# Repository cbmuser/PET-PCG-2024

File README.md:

# PET-PCG-2024
In the early 80th HAL Laboratory in Japan created a programmable character set generator and sound device for PET/CBM computers. This used the userport and the charater-socket for connection. So it was very easy to use with the first BASIC 1 machines. 
Mike Naberenzy reversed the logic and reassembled the software. A big thanks for that !  
http://mikenaberezny.com/hardware/pet-cbm/hal-pcg-6500-graphics-board/

It's also possible to rebuild the original hardware: https://github.com/InsaneDruid/PCG-6500 for the early BASIC1-machines. There you'll find also other usefull stuff for your PET.

My version fits into the newer dynamic PET-board (CBM 2001/3001) and uses DMA-access at **$a000** or $9000 for transfering the chars. There is no CB2-sound, I want to combine this in the future with a joystick-adapter at the userport.

You can use a IDT7130 in DIP or PLCC52. **You only need one of them !**  
The actual hardware is not tested in all cases (on/off function). Basically it works and new software is under construction, also some games from the HAL-adapter will be patched to this version. The board-routing was done in development-progress, so it works, but it's not the best it can be.  

**This is open hard- and software. Use it on your own risc. There is no warranty at all !**

The first board for development. The first idea was to use banking for addressing the whole ram and the bigger IDT7132. I've kicked this because no one will ever write software for that.

The char-rom and the connection to the socket fits on the solder-side.

A first character-editor 

It uses $a000 for the DMA. If you want to compile it for $9000 use the ACME Cross-Assembler. https://sourceforge.net/projects/acme-crossass/

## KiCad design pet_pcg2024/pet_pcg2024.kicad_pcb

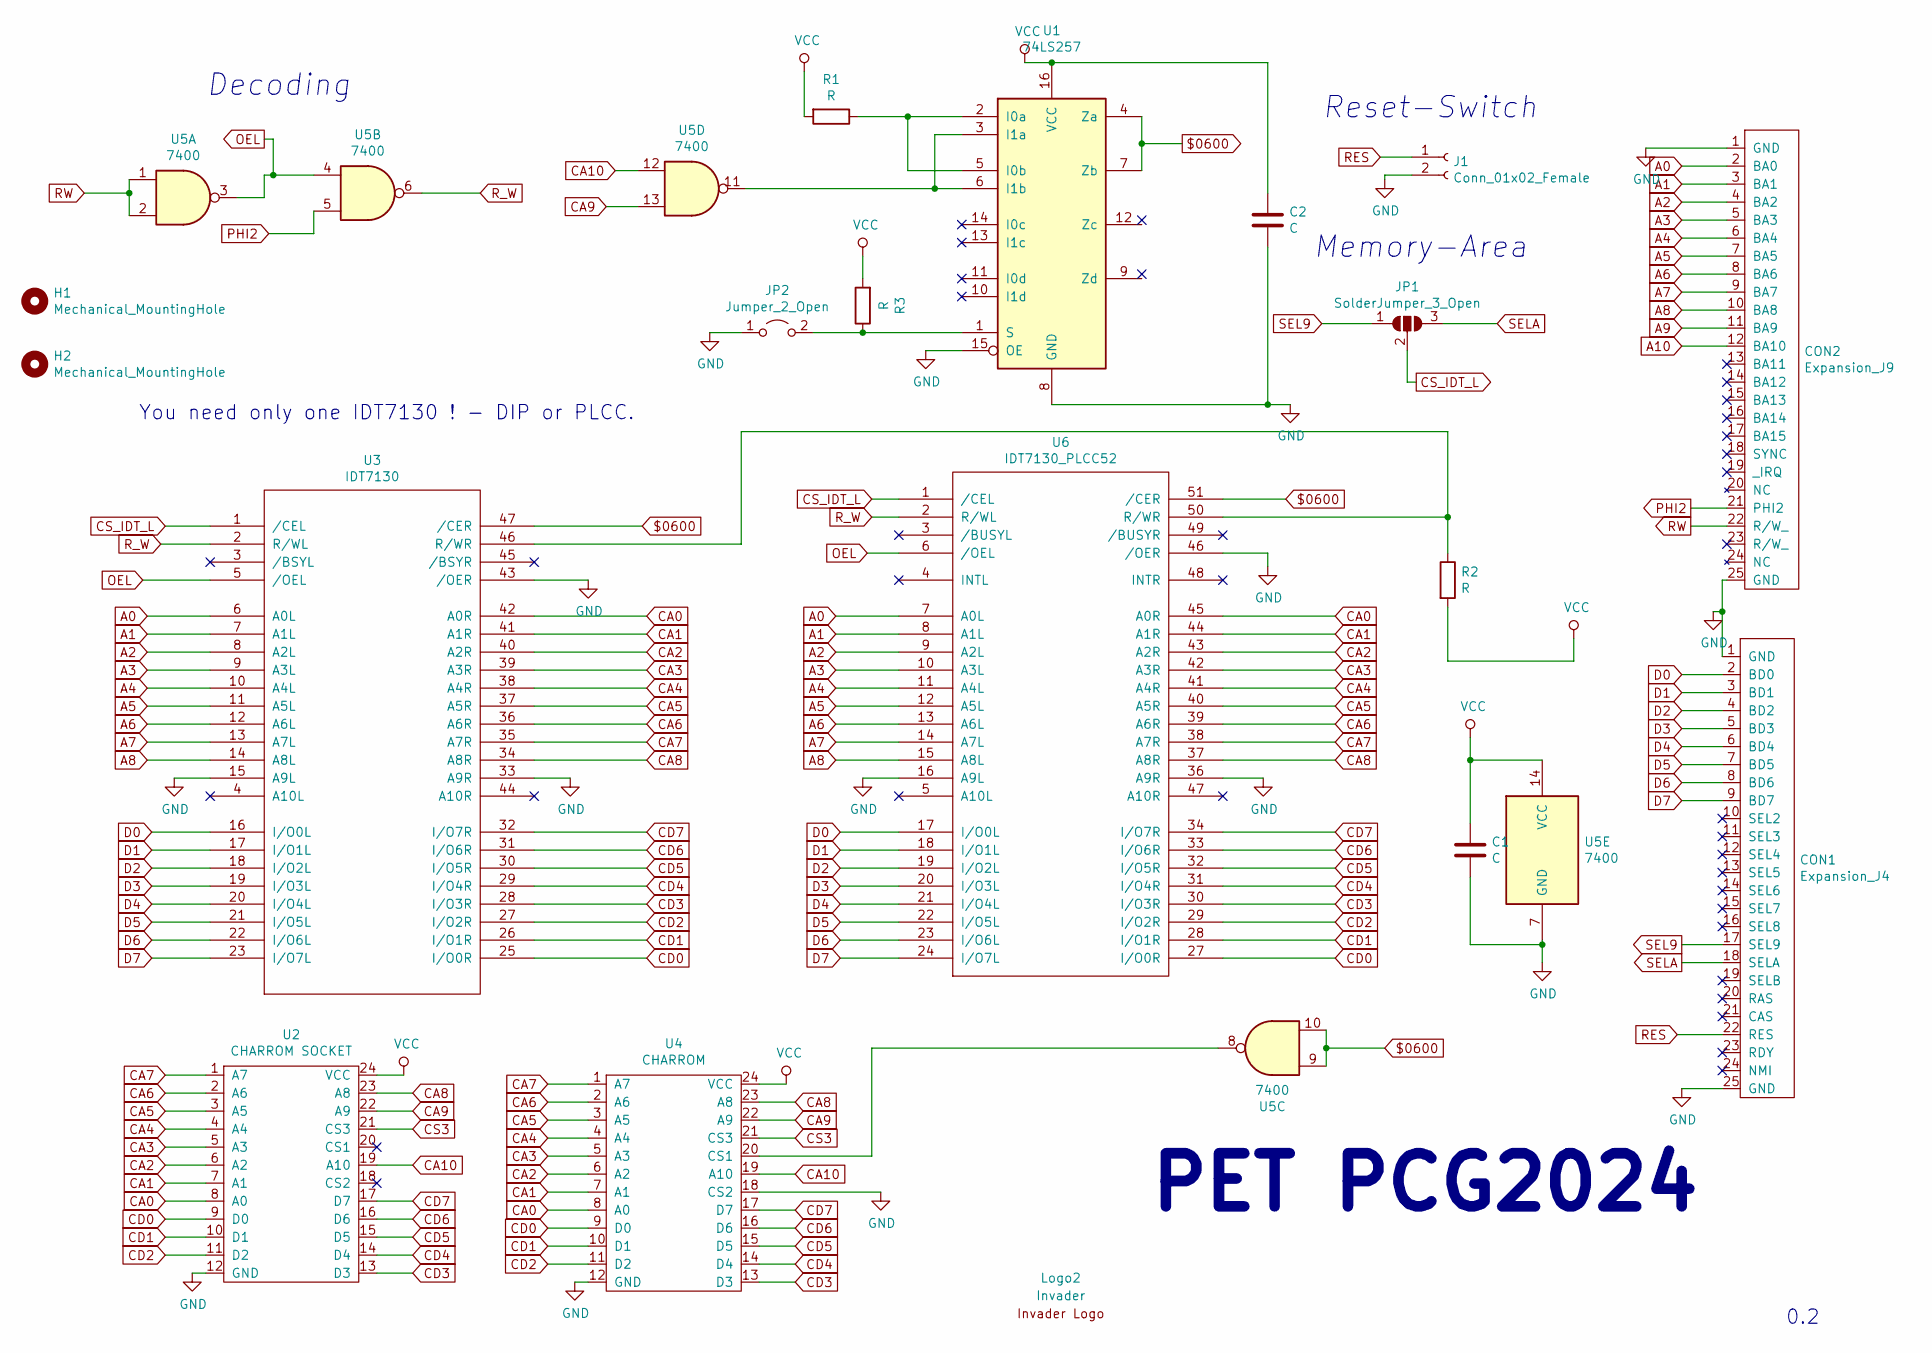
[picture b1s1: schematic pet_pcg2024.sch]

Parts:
C1, C2: C; C_Disc_D3.0mm_W1.6mm_P2.50mm
CON1: Expansion_J4; PET_EXPANSION_J4
CON2: Expansion_J9; PET_EXPANSION_J9
H1, H2: Mechanical_MountingHole; MountingHole_3.2mm_M3
J1: Conn_01x02_Female; PinHeader_1x02_P2.54mm_Vertical
JP1: SolderJumper_3_Open; SolderJumper-3_P1.3mm_Open_Pad1.0x1.5mm
JP2: Jumper_2_Open; PinHeader_1x02_P2.54mm_Vertical
Logo2: Invader; Invader_klein
R1, R3: R; R_Axial_DIN0204_L3.6mm_D1.6mm_P2.54mm_Vertical
R2: R; R_Axial_DIN0204_L3.6mm_D1.6mm_P1.90mm_Vertical
U1: 74LS257; DIP-16_W7.62mm
U2: CHARROM SOCKET; DIP-24_W15.24mm
U3: IDT7130; DIP-48_W15.24mm
U4: CHARROM; DIP-24_W15.24mm_Socket
U5: 7400; DIP-14_W7.62mm
U6: IDT7130_PLCC52; PLCC-52_THT-Socket

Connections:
$0600: U1.4 (Za), U1.7 (Zb), U3.47 (/CER), U5.9, U5.10, U6.51 (/CER)
A0: CON2.2 (BA0), U3.6 (A0L), U6.7 (A0L)
A1: CON2.3 (BA1), U3.7 (A1L), U6.8 (A1L)
A2: CON2.4 (BA2), U3.8 (A2L), U6.9 (A2L)
A3: CON2.5 (BA3), U3.9 (A3L), U6.10 (A3L)
A4: CON2.6 (BA4), U3.10 (A4L), U6.11 (A4L)
A5: CON2.7 (BA5), U3.11 (A5L), U6.12 (A5L)
A6: CON2.8 (BA6), U3.12 (A6L), U6.13 (A6L)
A7: CON2.9 (BA7), U3.13 (A7L), U6.14 (A7L)
A8: CON2.10 (BA8), U3.14 (A8L), U6.15 (A8L)
A9: CON2.11 (BA9)
A10: CON2.12 (BA10)
CA0: U2.8 (A0), U3.42 (A0R), U4.8 (A0), U6.45 (A0R)
CA1: U2.7 (A1), U3.41 (A1R), U4.7 (A1), U6.44 (A1R)
CA2: U2.6 (A2), U3.40 (A2R), U4.6 (A2), U6.43 (A2R)
CA3: U2.5 (A3), U3.39 (A3R), U4.5 (A3), U6.42 (A3R)
CA4: U2.4 (A4), U3.38 (A4R), U4.4 (A4), U6.41 (A4R)
CA5: U2.3 (A5), U3.37 (A5R), U4.3 (A5), U6.40 (A5R)
CA6: U2.2 (A6), U3.36 (A6R), U4.2 (A6), U6.39 (A6R)
CA7: U2.1 (A7), U3.35 (A7R), U4.1 (A7), U6.38 (A7R)
CA8: U2.23 (A8), U3.34 (A8R), U4.23 (A8), U6.37 (A8R)
CA9: U2.22 (A9), U4.22 (A9), U5.13
CA10: U2.19 (A10), U4.19 (A10), U5.12
CD0: U2.9 (D0), U3.25 (I/O0R), U4.9 (D0), U6.27 (I/O0R)
CD1: U2.10 (D1), U3.26 (I/O1R), U4.10 (D1), U6.28 (I/O1R)
CD2: U2.11 (D2), U3.27 (I/O2R), U4.11 (D2), U6.29 (I/O2R)
CD3: U2.13 (D3), U3.28 (I/O3R), U4.13 (D3), U6.30 (I/O3R)
CD4: U2.14 (D4), U3.29 (I/O4R), U4.14 (D4), U6.31 (I/O4R)
CD5: U2.15 (D5), U3.30 (I/O5R), U4.15 (D5), U6.32 (I/O5R)
CD6: U2.16 (D6), U3.31 (I/O6R), U4.16 (D6), U6.33 (I/O6R)
CD7: U2.17 (D7), U3.32 (I/O7R), U4.17 (D7), U6.34 (I/O7R)
CS3: U2.21 (CS3), U4.21 (CS3)
CS_IDT_L: JP1.2 (C), U3.1 (/CEL), U6.1 (/CEL)
D0: CON1.2 (BD0), U3.16 (I/O0L), U6.17 (I/O0L)
D1: CON1.3 (BD1), U3.17 (I/O1L), U6.18 (I/O1L)
D2: CON1.4 (BD2), U3.18 (I/O2L), U6.19 (I/O2L)
D3: CON1.5 (BD3), U3.19 (I/O3L), U6.20 (I/O3L)
D4: CON1.6 (BD4), U3.20 (I/O4L), U6.21 (I/O4L)
D5: CON1.7 (BD5), U3.21 (I/O5L), U6.22 (I/O5L)
D6: CON1.8 (BD6), U3.22 (I/O6L), U6.23 (I/O6L)
D7: CON1.9 (BD7), U3.23 (I/O7L), U6.24 (I/O7L)
GND: C1.2, C2.2, CON1.1 (GND), CON1.25 (GND), CON2.1 (GND), CON2.25 (GND), J1.2, JP2.1 (A), U1.8 (GND), U1.15 (OE), U2.12 (GND), U3.15 (A9L), U3.24 (GND), U3.33 (A9R), U3.43 (/OER), U4.12 (GND), U4.18 (CS2), U5.7 (GND), U6.16 (A9L), U6.26 (GND), U6.36 (A9R), U6.46 (/OER)
unnamed: JP2.2 (B), R3.1, U1.1 (S)
unnamed: R1.1, U1.2 (I0a), U1.5 (I0b)
unnamed: R2.1, U3.46 (R/WR), U6.50 (R/WR)
unnamed: U1.3 (I1a), U1.6 (I1b), U5.11
unnamed: U4.20 (CS1), U5.8
OEL: U3.5 (/OEL), U5.3, U5.4, U6.6 (/OEL)
PHI2: CON2.21 (PHI2), U5.5
RES: CON1.22 (RES), J1.1
RW: CON2.22 (R/W_), U5.1, U5.2
R_W: U3.2 (R/WL), U5.6, U6.2 (R/WL)
SEL9: CON1.17 (SEL9), JP1.1 (A)
SELA: CON1.18 (SELA), JP1.3 (B)
VCC: C1.1, C2.1, R1.2, R2.2, R3.2, U1.16 (VCC), U2.24 (VCC), U3.48 (VCC), U4.24 (VCC), U5.14 (VCC), U6.52 (VCC)

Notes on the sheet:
PET PCG2024
Reset-Switch
Decoding
Memory-Area
You need only one IDT7130 ! - DIP or PLCC.
0.2

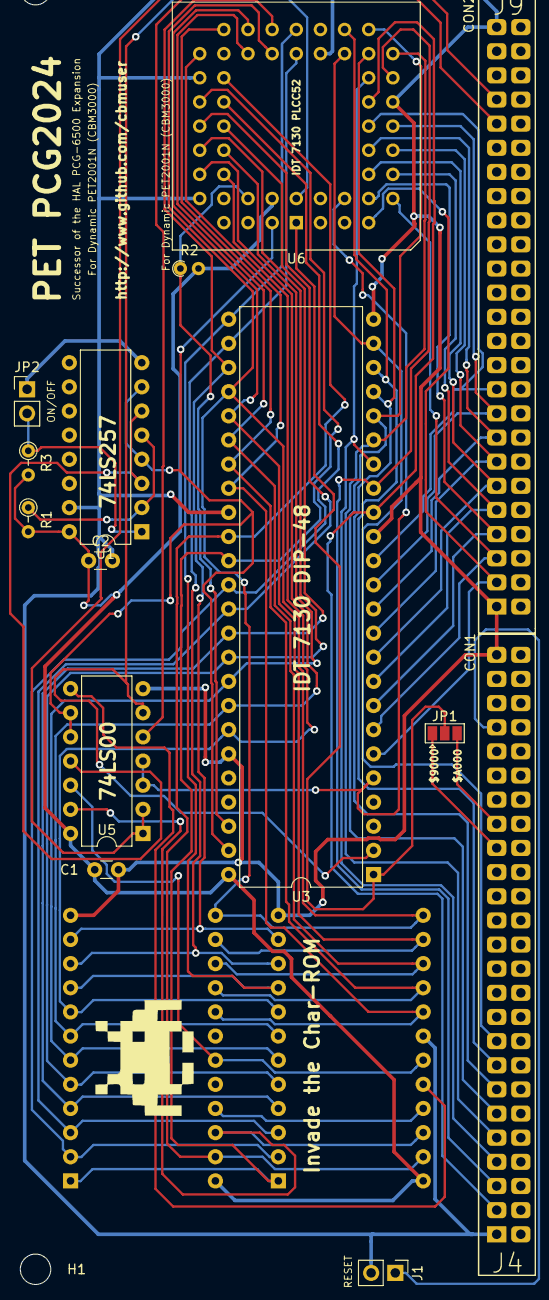
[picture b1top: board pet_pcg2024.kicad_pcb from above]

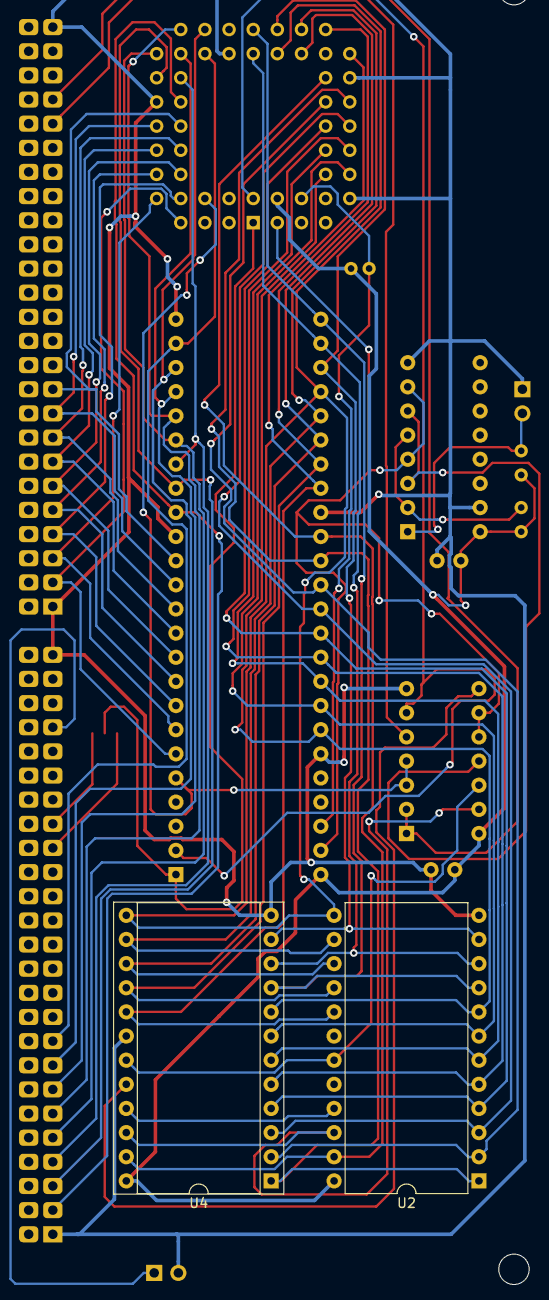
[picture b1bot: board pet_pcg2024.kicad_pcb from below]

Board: 2 copper layers, 19 parts (2 on the bottom side), 53 nets.

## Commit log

2024-04-14 Basic 2 Sources
2024-04-14 PET 2001N Screenshot
2024-04-14 Tools for BASIC 2
2024-04-15 Update charedit.asm
    fix
2024-04-15 Add files via upload
    Fixed a bug
2024-04-17 Update charedit.asm
    some optimizing and shrinking the source
2024-07-07 Schematic and board
2024-07-07 Schematic
2024-07-07 Update charedit.asm
    small fix
2024-07-07 Development-Version
2024-07-07 Development-Version solder-side
2024-07-13 Patched HAL-Software
2024-07-21 8x8 Char Pixeler
    For Tiles and Chars
2024-07-21 Pixeler for Basic 4
    For Tiles and Chars
2024-07-21 Update pixeler_b4.asm
    minor change
